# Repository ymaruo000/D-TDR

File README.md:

# D-TDR: Duty-Ratio Time Domain Reflectometry

A low-cost, open-source soil moisture sensor that measures apparent relative permittivity (Ka) using duty-ratio modulation of TDR pulse travel time.

## Overview

D-TDR converts the two-way electromagnetic travel time in a TDR probe into a DC voltage proportional to the square root of Ka, using three analog circuits:

1. **Oscillator** — generates a repetitive pulse into the waveguide probe
2. **Comparator** — encodes the travel time as a duty ratio
3. **Integrator** — converts the duty ratio into a stable DC voltage

The output voltage V_DTDR is linearly proportional to sqrt(Ka), enabling direct use of established Ka-theta calibration relationships developed for conventional TDR.

## Features

- No waveform digitization or dedicated TDR instrumentation required
- Medium-independent calibration using air and water only
- Full compatibility with established Ka-theta relationships (e.g., Topp et al., 1980)

## Repository Contents

```
kicad/          KiCad project files (schematic, PCB layout)
docs/
  TDR20260220.pdf       Circuit schematic (PDF)
  TDR20260220_pcb.pdf   PCB layout (PDF)
  TDR20260220.csv       Bill of materials
```

## Requirements

- [KiCad](https://www.kicad.org/) 9.0 or later to open and edit the design files (the files were saved with KiCad 9.0 and cannot be opened in earlier versions)
- PDF viewer to browse the schematic and PCB layout

## Notes on Components

- The comparator (U2, NJM360, Nisshinbo Micro Devices) has been discontinued.

## Reference

Maruo, Y., Fujita, Y. and Noborio, K. (2026): A low-cost Duty-ratio Time Domain Reflectometry (D-TDR) for soil permittivity measurement. J. Jpn. Soc. Soil Phys., 164 (in press).

## License

This project is licensed under the [CERN Open Hardware Licence Version 2 - Permissive (CERN-OHL-P v2)](https://ohwr.org/cern_ohl_p_v2.txt). See [LICENSE](LICENSE) for details.

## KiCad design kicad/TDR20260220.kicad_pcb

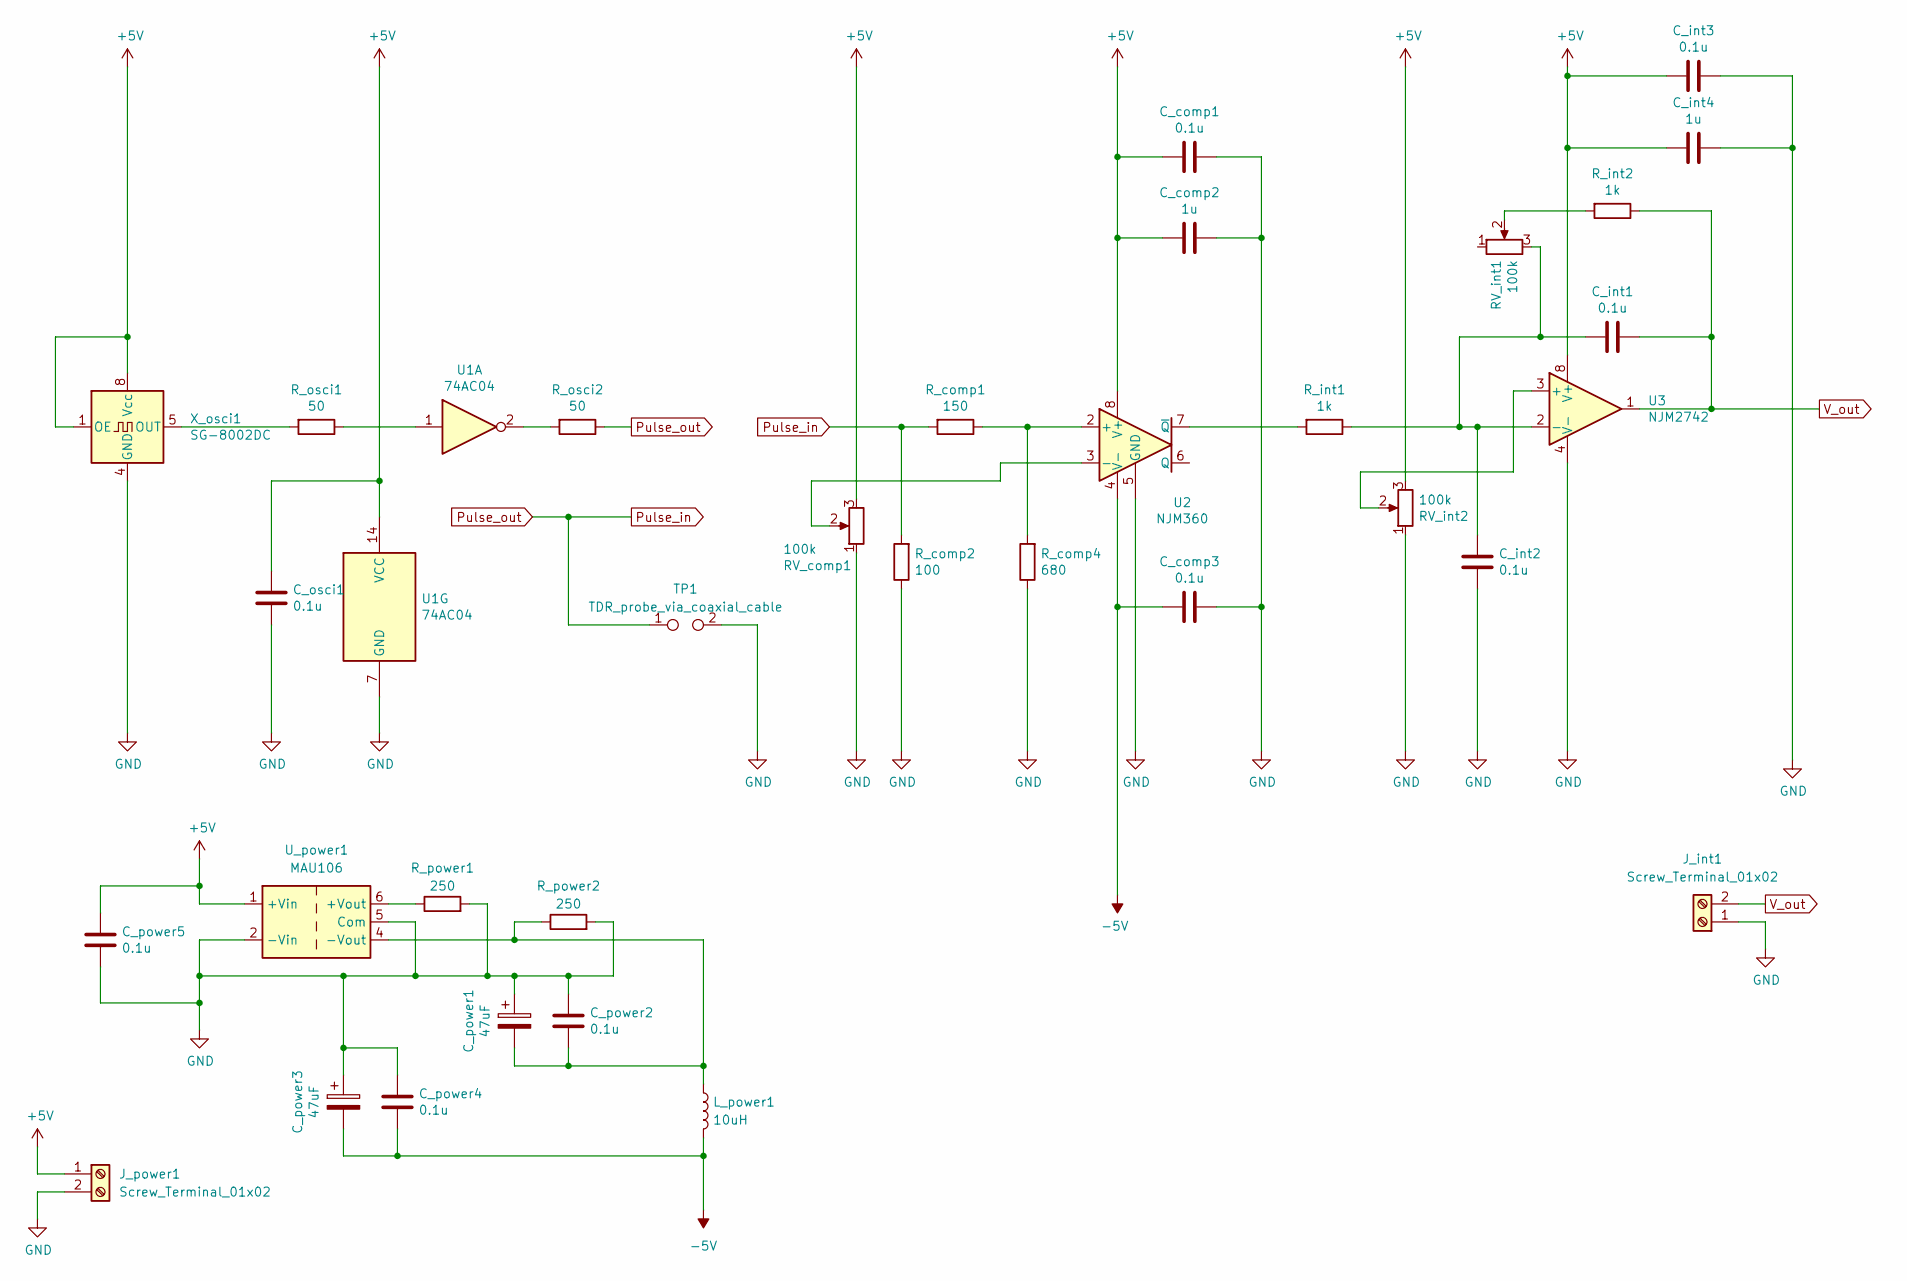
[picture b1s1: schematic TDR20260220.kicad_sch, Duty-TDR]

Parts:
C_comp1, C_comp3: 0.1u; C_Rect_L4.6mm_W3.0mm_P2.50mm_MKS02_FKP02
C_comp2: 1u; C_Rect_L4.6mm_W3.0mm_P2.50mm_MKS02_FKP02
C_int1, C_int2, C_int3: 0.1u; C_Rect_L4.6mm_W3.0mm_P2.50mm_MKS02_FKP02
C_int4: 1u; C_Rect_L4.6mm_W3.0mm_P2.50mm_MKS02_FKP02
C_osci1: 0.1u; C_Rect_L4.6mm_W3.0mm_P2.50mm_MKS02_FKP02
C_power1, C_power3: 47uF; CP_Radial_D5.0mm_P2.00mm
C_power2, C_power4, C_power5: 0.1u; C_Rect_L4.6mm_W3.0mm_P2.50mm_MKS02_FKP02
J_int1: Screw_Terminal_01x02; TerminalBlock_bornier-2_P5.08mm
J_power1: Screw_Terminal_01x02; TerminalBlock_bornier-2_P5.08mm
L_power1: 10uH; L_Radial_L12.6mm_W12.6mm_Px9.52mm_Py9.52mm_Pulse_LP-37
RV_comp1: 100k; Potentiometer_Bourns_3266P_Horizontal
RV_int1, RV_int2: 100k; Potentiometer_Bourns_3266P_Horizontal
R_comp1: 150; R_Axial_DIN0207_L6.3mm_D2.5mm_P7.62mm_Horizontal
R_comp2: 100; R_Axial_DIN0207_L6.3mm_D2.5mm_P7.62mm_Horizontal
R_comp4: 680; R_Axial_DIN0207_L6.3mm_D2.5mm_P7.62mm_Horizontal
R_int1, R_int2: 1k; R_Axial_DIN0207_L6.3mm_D2.5mm_P7.62mm_Horizontal
R_osci1, R_osci2: 50; R_Axial_DIN0207_L6.3mm_D2.5mm_P7.62mm_Horizontal
R_power1, R_power2: 250; R_Axial_DIN0207_L6.3mm_D2.5mm_P7.62mm_Horizontal
TP1: TDR_probe_via_coaxial_cable; TestPoint_2Pads_Pitch5.08mm_Drill1.3mm
U1: 74AC04; CERDIP-14_W7.62mm_SideBrazed_Socket
U2: NJM360; CERDIP-8_W7.62mm_SideBrazed_Socket
U3: NJM2742; CERDIP-8_W7.62mm_SideBrazed_Socket
U_power1: MAU106; Converter_DCDC_TRACO_TBA2-xxxx_Dual_THT
X_osci1: SG-8002DC; CERDIP-8_W7.62mm_SideBrazed_Socket

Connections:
+5V: C_comp1.1, C_comp2.1, C_int3.1, C_int4.1, C_osci1.2, C_power5.2, J_power1.1, RV_comp1.3, RV_int2.3, U1.14 (VCC), U2.8 (V+), U3.8 (V+), U_power1.1 (+Vin), X_osci1.1 (OE), X_osci1.8 (Vcc)
-5V: C_comp3.1, C_power3.2, C_power4.1, L_power1.2, U2.4 (V-)
GND: C_comp1.2, C_comp2.2, C_comp3.2, C_int2.2, C_int3.2, C_int4.2, C_osci1.1, C_power1.1, C_power2.2, C_power3.1, C_power4.2, C_power5.1, J_int1.1, J_power1.2, RV_comp1.1, RV_int2.1, R_comp2.1, R_comp4.1, R_power1.2, R_power2.2, TP1.2, U1.7 (GND), U2.5 (GND), U3.4 (V-), U_power1.2 (-Vin), U_power1.5 (Com), X_osci1.4 (GND)
unnamed: RV_int1.2, R_int2.2
unnamed: R_osci1.1, U1.1
unnamed: R_osci2.2, U1.2
unnamed: R_comp1.1, R_comp4.2, U2.2 (+)
unnamed: RV_comp1.2, U2.3 (-)
unnamed: R_int1.2, U2.7 (~Q)
unnamed: RV_int2.2, U3.3 (+)
unnamed: C_int1.1, C_int2.1, RV_int1.3, R_int1.1, U3.2 (-)
unnamed: R_power1.1, U_power1.6 (+Vout)
unnamed: C_power1.2, C_power2.1, L_power1.1, R_power2.1, U_power1.4 (-Vout)
unnamed: R_osci1.2, X_osci1.5 (OUT)
Pulse_in: R_comp1.2, R_comp2.2, R_osci2.1, TP1.1
V_out: C_int1.2, J_int1.2, R_int2.1, U3.1

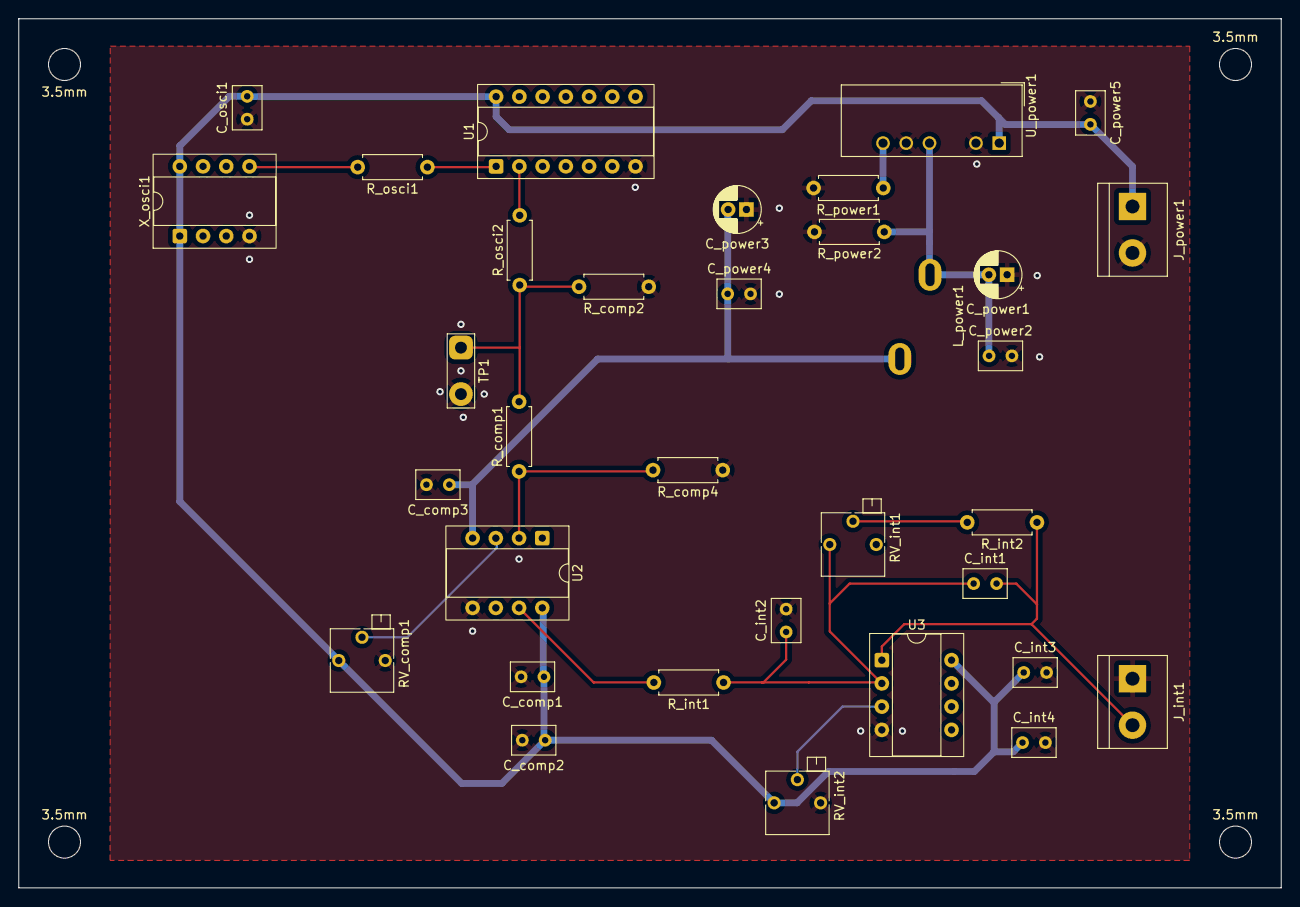
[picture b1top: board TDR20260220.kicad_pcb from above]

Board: 2 copper layers, 138.0 x 95.0 mm, 38 parts (0 on the bottom side), 16 nets.

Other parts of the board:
3.5mm, 3.5mm#2, 3.5mm#3, 3.5mm#4: MountingHole_3.5mm

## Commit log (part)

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2026-03-22 Initial commit: D-TDR circuit design files
    - KiCad project files (schematic, PCB layout)
    - Circuit schematic and PCB layout PDFs
    - Bill of materials (CSV)
    - README and CERN-OHL-P v2 license
